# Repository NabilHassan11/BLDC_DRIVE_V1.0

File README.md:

# BLDC Drive

A 3-phase Brushless DC (BLDC) motor driver PCB designed in KiCad, capable of handling **12V** supply voltage at **10–25A** continuous phase current.

---

## 📸 Board Preview

<!-- Replace the placeholder below with your actual board image -->
<!-- > 📷 **[Insert top-view board photo or 3D render here]** -->

---

## ✨ Features

- **Input Voltage:** 12V
- **Output Current:** 10–25A (per phase, depending on thermal management)
- **Gate Driver:** IR2110 half-bridge drivers (×3 — one per phase)
- **Power MOSFETs:** IRFZ44VZPBF N-channel MOSFETs in a 3-phase full-bridge configuration (6× total)
- **Current Sensing:** INA180A3 rail-to-rail current sense amplifiers
- **Bulk Decoupling:** 470µF electrolytic capacitors for supply filtering
- **EMI Filtering:** WE-CBF 0805 ferrite beads and 100nF bypass capacitors
- **Board Size:** 80mm × 80mm, 2-layer PCB
- **Connectors:** JST XH series
- **Designed with:** KiCad 8.0

---

## 🖼 Schematic

<!-- Add schematic image or PDF link below -->
> 📐 **[Insert schematic screenshot or link here]**

<!-- Or link to the PDF: -->
<!-- [View Full Schematic (PDF)](BLDC_Drive/plots/BLDC_Drive__Assembly.pdf) -->
-->

---

## 🔩 Bill of Materials (BOM)

| Designator | Component | Value / Part Number | Description |
|---|---|---|---|
| Q1–Q6 | N-Channel MOSFET | IRFZ44VZPBF | Power switch, TO-220 |
| U1–U3 | Gate Driver | IR2110 | Half-bridge gate driver |
| U4–U6 | Current Sense Amp | INA180A3 | Rail-to-rail, 100V/V gain, SOT-23-5 |
| C_bulk | Electrolytic Cap | 470µF | Bulk supply decoupling |
| C_bypass | Ceramic Cap | 100nF | High-freq bypass |
| C_gate | Ceramic Cap | 1µF / 10µF | Gate drive bootstrap / filtering |
| R_sense | Shunt Resistor | 5mΩ 3W | Phase current sensing |
| R_gate | Resistor | 5Ω / 10Ω / 20Ω | Gate resistance |
| FB1–FBx | Ferrite Bead | WE-CBF 0805, 600Ω@100MHz | EMI filtering |
| J_motor | JST B9B-XH-A | 9-pin | Motor phase + hall sensor connector |
| J_signal | JST B2B-XH-A | 2-pin | Signal/control connector |
| — | Screw Terminals | 2-pin, 3-pin | Power input/output terminals |

> 📋 **Full interactive BOM:** [`BLDC_Drive/bom/ibom.html`](BLDC_Drive/bom/ibom.html)

---

## 📁 Repository Structure

```
BLDC_Drive/
├── BLDC_Drive/
│   ├── BLDC_Drive.kicad_sch         # Schematic
│   ├── BLDC_Drive.kicad_pcb         # PCB layout
│   ├── BLDC_Drive.kicad_pro         # KiCad project file
│   ├── bom/
│   │   └── ibom.html                # Interactive BOM
│   ├── Drill Files/                 # PTH and NPTH drill files
│   ├── gerber_to_order/             # Ready-to-order Gerbers
│   │   ├── BLDC_Drive_80.0x80.0mm_for_JLCPCB/
│   │   ├── BLDC_Drive_80.0x80.0mm_for_Elecrow/
│   │   ├── BLDC_Drive_80.0x80.0mm_for_PCBWay/
│   │   └── BLDC_Drive_80.0x80.0mm_for_FusionPCB/
│   └── plots/
│       └── BLDC_Drive__Assembly.pdf # Assembly drawing
├── AOD4184A/                        # KiCad library: AOD4184A MOSFET
├── IRFZ44VZPBF/                     # KiCad library: IRFZ44VZPBF MOSFET
├── LIB_DRV8353SRTAR/                # KiCad library: DRV8353 gate driver
├── B2B-XH-A/ & B9B-XH-A/           # KiCad library: JST connectors
├── LM358P/                          # KiCad library: LM358 op-amp
├── WE-CBF_0805/                     # KiCad library: ferrite bead
└── cap_calculator.jsx               # Bootstrap capacitor calculator tool
```

---

## 🖼 PCB Layout

<!-- Add PCB layout images below -->

---

## 🚀 Getting Started

### Requirements

- [KiCad 8.0](https://www.kicad.org/) or later
- A 12V DC power supply rated for at least 25A
- PWM control signals (typically from a microcontroller or dedicated BLDC controller)

### Opening the Project

1. Clone or download this repository.
2. Open KiCad and select **File → Open Project**.
3. Navigate to `BLDC_Drive/BLDC_Drive.kicad_pro`.
4. Import the custom component libraries from the component folders (see `how-to-import.htm` inside each folder).

### Ordering PCBs

Pre-generated Gerber files are available for major manufacturers inside `BLDC_Drive/gerber_to_order/`. Simply upload the appropriate `.zip` file to your fab of choice:

| Manufacturer | Gerber Package |
|---|---|
| JLCPCB | `BLDC_Drive_80.0x80.0mm_for_JLCPCB.zip` |
| PCBWay | `BLDC_Drive_80.0x80.0mm_for_PCBWay.zip` |
| Elecrow | `BLDC_Drive_80.0x80.0mm_for_Elecrow.zip` |
| FusionPCB | `BLDC_Drive_80.0x80.0mm_for_FusionPCB.zip` |

Recommended PCB specs: **2 layers, 2oz copper, HASL or ENIG finish.**

---

## ⚡ Electrical Specifications

| Parameter | Value |
|---|---|
| Supply Voltage (V_bus) | 12V |
| Continuous Phase Current | 10–25A |
| MOSFET V_DS rating | 60V (IRFZ44VZPBF) |
| MOSFET I_D rating | 55A (IRFZ44VZPBF) |
| Gate Driver Bootstrap voltage | 12V |
| Current sense gain | 100 V/V (INA180A3) |
| Shunt resistance | 5mΩ |

---

## ⚠️ Warnings & Safety Notes

- Always ensure proper heat sinking on the power MOSFETs (Q1–Q6) when operating above 10A.
- Do not exceed **12V** on the V_bus input without verifying all component voltage ratings.
- Verify gate drive bootstrap capacitor values using the included `cap_calculator.jsx` tool before assembling.
- The board does not include overcurrent protection hardware — implement this in firmware or add an external fuse rated for your load.
- This board is designed for **DC brushless motors only**. Do not connect it to AC loads.

---

## 🔧 Assembly Notes

> 🔩 **[Insert assembled board photo here]**

<!-- Example:

-->

- Begin soldering with the smallest SMD components first (ferrite beads, bypass caps, SOT-23 ICs).
- Solder power MOSFETs and screw terminals last.
- Refer to the interactive BOM (`bom/ibom.html`) for component placement guidance.
- The assembly drawing PDF (`plots/BLDC_Drive__Assembly.pdf`) can be printed as a reference during assembly.

---

## 👤 Author

**Nabil Hassan**
Revision date: 2026-03-09

---

## 🤝 Contributing

Pull requests and issue reports are welcome. If you find a bug in the schematic or layout, please open an issue with a description and reference designators.

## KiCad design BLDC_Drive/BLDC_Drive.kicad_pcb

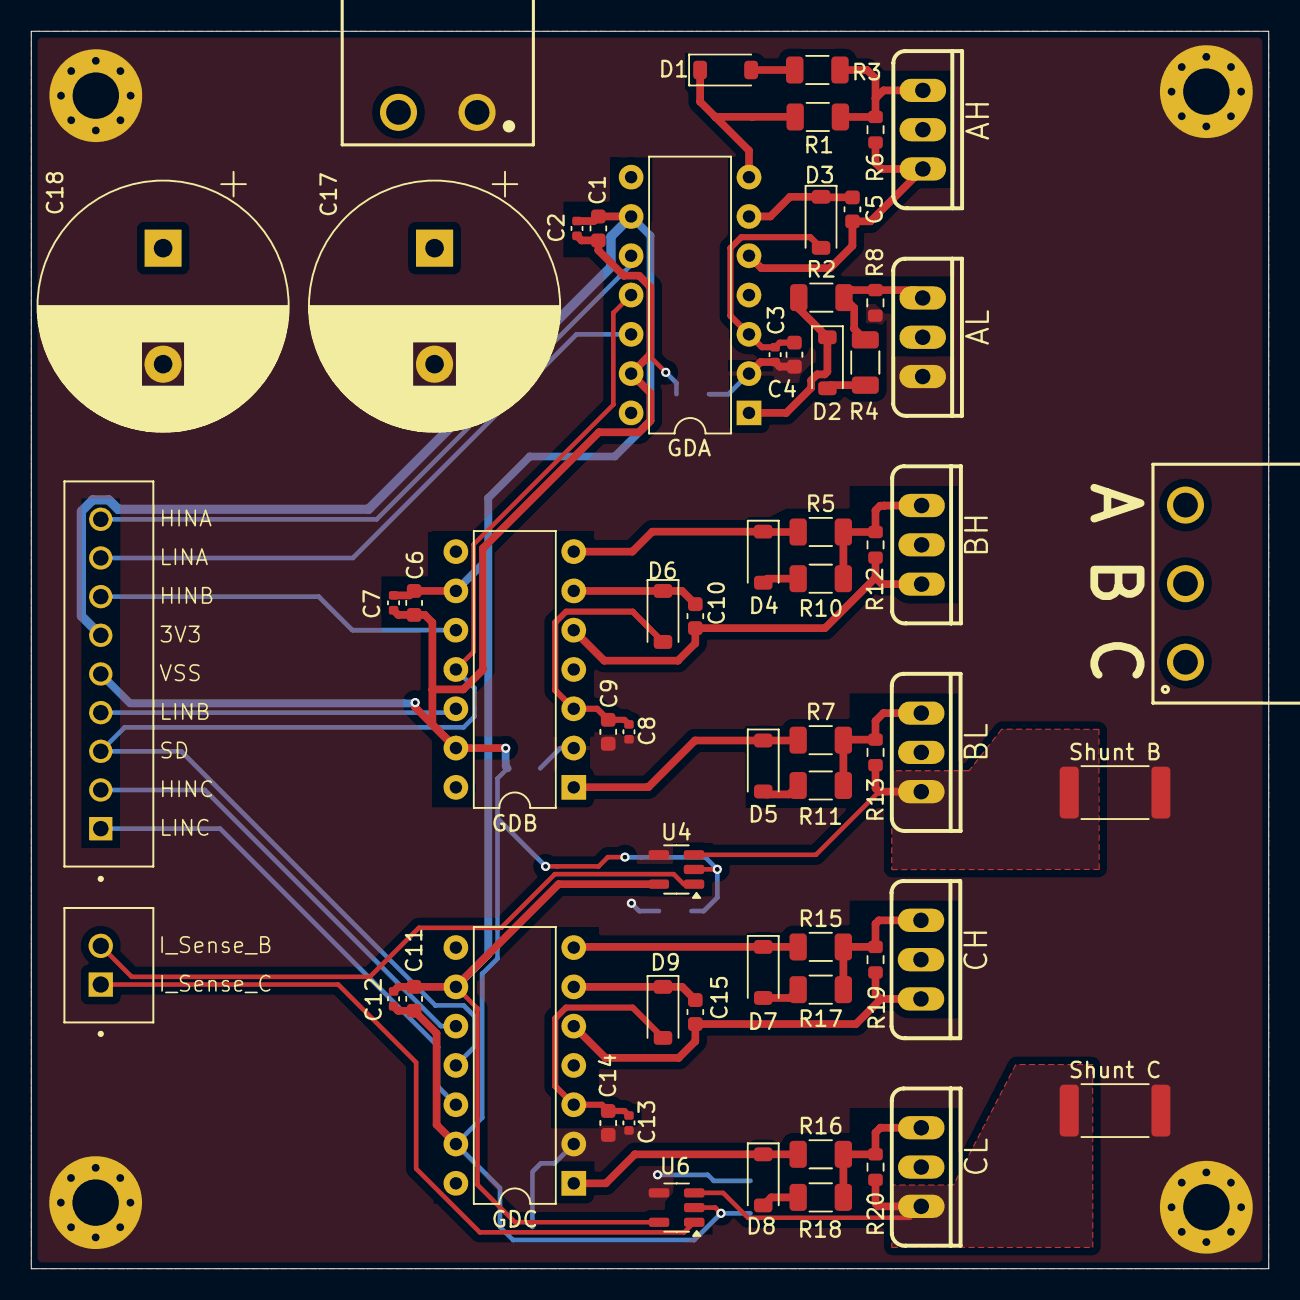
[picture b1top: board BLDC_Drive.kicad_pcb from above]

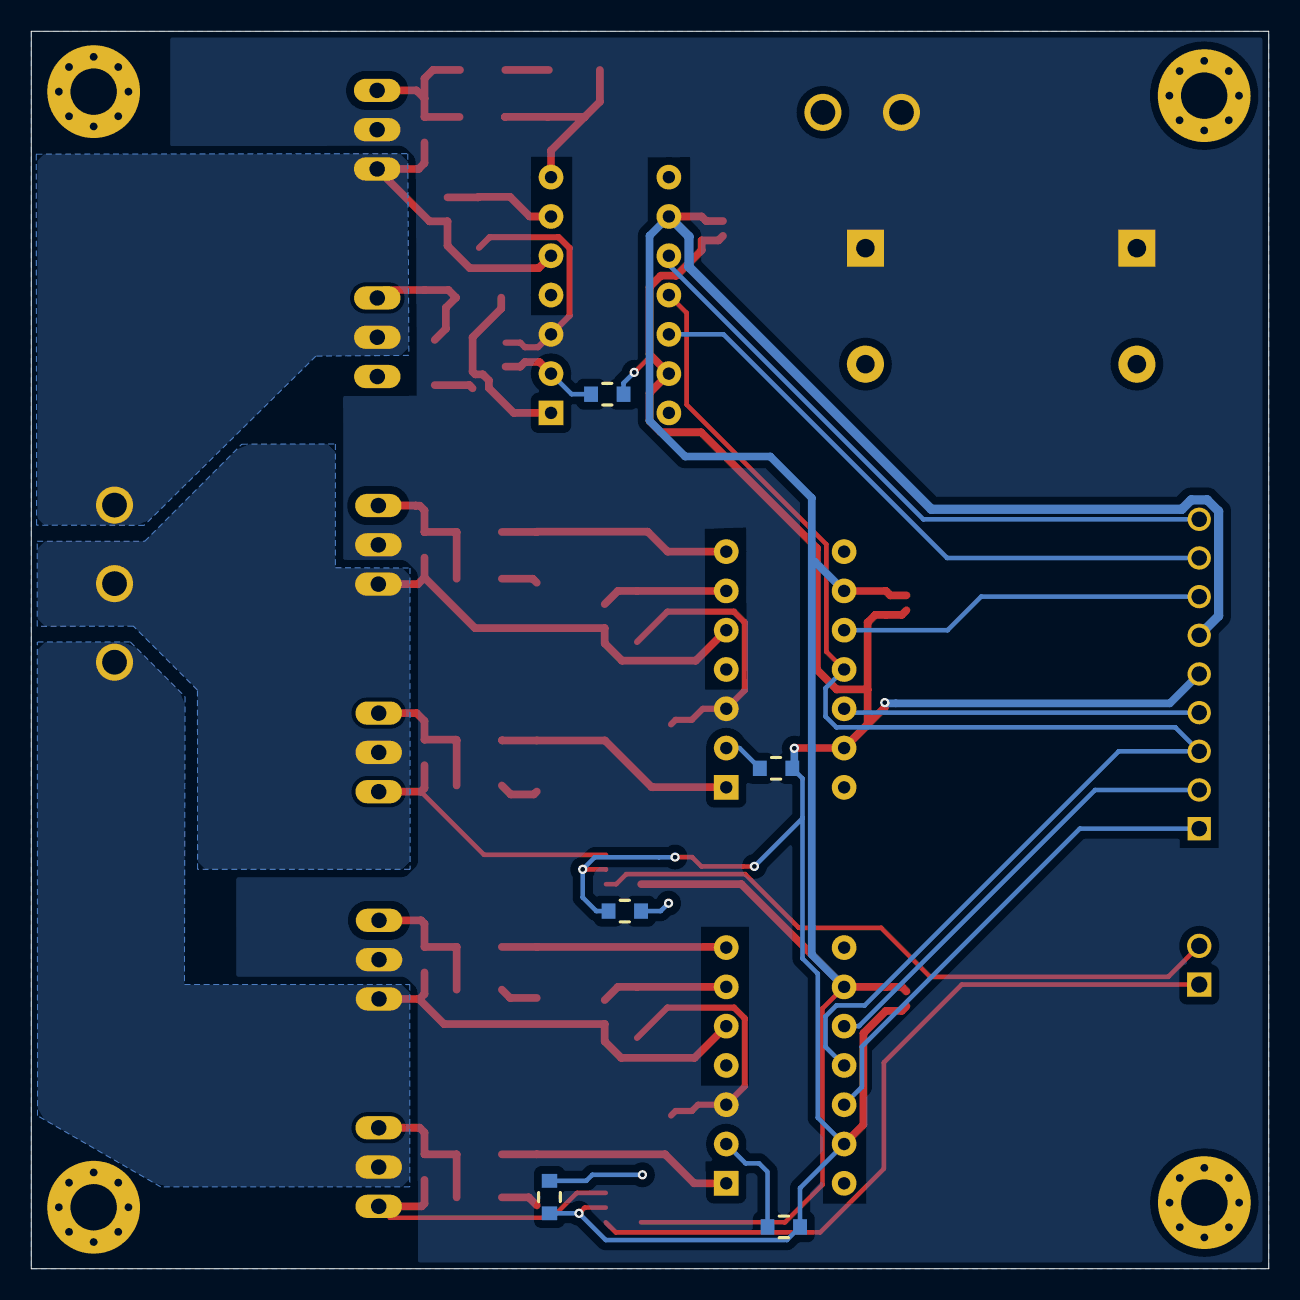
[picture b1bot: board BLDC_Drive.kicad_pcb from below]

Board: 2 copper layers, 80.0 x 80.0 mm, 70 parts (5 on the bottom side), 39 nets.

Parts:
AH: IRFZ44VZPBF; TO-220
AL: IRFZ44VZPBF; TO-220
BH: IRFZ44VZPBF; TO-220
BL: IRFZ44VZPBF; TO-220
C1, C4, C6, C9, C11, C14: 10uF; C_0603_1608Metric
C2, C3, C7, C8, C12, C13: 100nF; C_0402_1005Metric
C5, C10, C15: 1uF; C_0603_1608Metric
C17, C18: 470uF; CP_Radial_D16.0mm_P7.50mm
CH: IRFZ44VZPBF; TO-220
CL: IRFZ44VZPBF; TO-220
D1, D2, D3, D4, D5, D6, D7, D8, D9: D; D_SOD-123
FB1, FB2, FB3, FB4, FB5: 600Ω @ 100MHz; WE-CBF_0805_W3.0
GDA: IR2110; DIP-14_W7.62mm
GDB: IR2110; DIP-14_W7.62mm
GDC: IR2110; DIP-14_W7.62mm
H1, H2, H3, H4: MountingHole_Pad; MountingHole_3mm_Pad_Via
J1: B2B-XH-A; JST_B2B-XH-A
J2: B9B-XH-A; JST_B9B-XH-A
J3: Screw_Terminal_01x02; 691313510002
J4: Screw_Terminal_01x03; 691312510003
R1, R2, R5, R7, R15, R16: 20; R_1206_3216Metric
R3, R4, R10, R17, R18: 10; R_1206_3216Metric
R6, R8, R12, R13, R19, R20: 10k; R_0603_1608Metric
R11: 5; R_1206_3216Metric
Shunt B: 5m 3W; R_2512_6332Metric
Shunt C: 5m 3W; R_2512_6332Metric
U4, U6: INA180A3; SOT-23-5

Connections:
+12V: AH.2, BH.2, C3.1, C4.1, C8.1, C9.1, C13.1, C14.1, C17.1, C18.1, CH.2, D3.2 (A), D6.2 (A), D9.2 (A), GDA.3 (VCC), GDB.3 (VCC), GDC.3 (VCC), J3.2
GHA: AH.1, R1.2, R3.2, R6.1
GHB: BH.1, R5.2, R10.2, R12.1
GHC: CH.1, R15.2, R17.2, R19.1
GLA: AL.1, R2.2, R4.1, R8.1
GLB: BL.1, R7.2, R11.1, R13.1
GLC: CL.1, R16.2, R18.1, R20.1
GND: AL.3, C3.2, C4.2, C8.2, C9.2, C13.2, C14.2, C17.2, C18.2, FB1.1, FB2.1, FB3.2, FB4.2, FB5.2, GDA.2 (COM), GDB.2 (COM), GDC.2 (COM), H1.1, H2.1, H3.1, H4.1, J3.1, R8.2, Shunt B.2, Shunt C.2, U4.4 (-), U6.4 (-)
HINA: GDA.10 (HIN), J2.9
HINB: GDB.10 (HIN), J2.7
HINC: GDC.10 (HIN), J2.2
I_Sense_B: J1.2, U4.1
I_Sense_B_P: BL.3, R13.2, Shunt B.1, U4.3 (+)
I_Sense_C: J1.1, U6.1
I_Sense_C_P: CL.3, R20.2, Shunt C.1, U6.3 (+)
LINA: GDA.12 (LIN), J2.8
LINB: GDB.12 (LIN), J2.4
LINC: GDC.12 (LIN), J2.1
unnamed: D1.2 (A), R3.1
unnamed: D1.1 (K), GDA.7 (HO), R1.1
unnamed: D2.2 (A), R4.2
unnamed: D2.1 (K), GDA.1 (LO), R2.1
unnamed: C5.1, D3.1 (K), GDA.6 (VB)
unnamed: D4.2 (A), R10.1
unnamed: D4.1 (K), GDB.7 (HO), R5.1
unnamed: D5.2 (A), R11.2
unnamed: D5.1 (K), GDB.1 (LO), R7.1
unnamed: C10.1, D6.1 (K), GDB.6 (VB)
unnamed: D7.2 (A), R17.1
unnamed: D7.1 (K), GDC.7 (HO), R15.1
unnamed: D8.2 (A), R18.2
unnamed: D8.1 (K), GDC.1 (LO), R16.1
unnamed: C15.1, D9.1 (K), GDC.6 (VB)
Phase_A: AH.3, AL.2, C5.2, GDA.5 (VS), J4.3, R6.2
Phase_B: BH.3, BL.2, C10.2, GDB.5 (VS), J4.2, R12.2
Phase_C: C15.2, CH.3, CL.2, GDC.5 (VS), J4.1, R19.2
SD: GDA.11 (SD), GDB.11 (SD), GDC.11 (SD), J2.3
VDD_3V3: C1.1, C2.1, C6.1, C7.1, C11.1, C12.1, GDA.9 (VDD), GDB.9 (VDD), GDC.9 (VDD), J2.6, U4.5 (V+), U6.5 (V+)
VSS_GND: C1.2, C2.2, C6.2, C7.2, C11.2, C12.2, FB1.2, FB2.2, FB3.1, FB4.1, FB5.1, GDA.13 (VSS), GDB.13 (VSS), GDC.13 (VSS), J2.5, U4.2 (GND), U6.2 (GND)

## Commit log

2026-05-03 Added PCB files
2026-05-03 Add README.md file
2026-05-03 Remove license section from README
    Removed placeholder for license information in README.
2026-05-03 Add link to BLDC Drive top view image in README
    Updated README to include a link to the BLDC Drive top view image.
2026-05-03 Fix image syntax in README for top view photo
2026-05-04 Update bldc_drive_top images
2026-05-04 Added BLDC DRIVE Image
2026-05-04 Revise connector details and power terminal description
    Updated connector information and clarified power terminal description.
2026-05-15 Update README to remove PCB image placeholder
    Removed placeholder for PCB top copper layer image.
